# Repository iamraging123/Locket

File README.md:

# Locket
A homemade model rocket with a bunch of cool features

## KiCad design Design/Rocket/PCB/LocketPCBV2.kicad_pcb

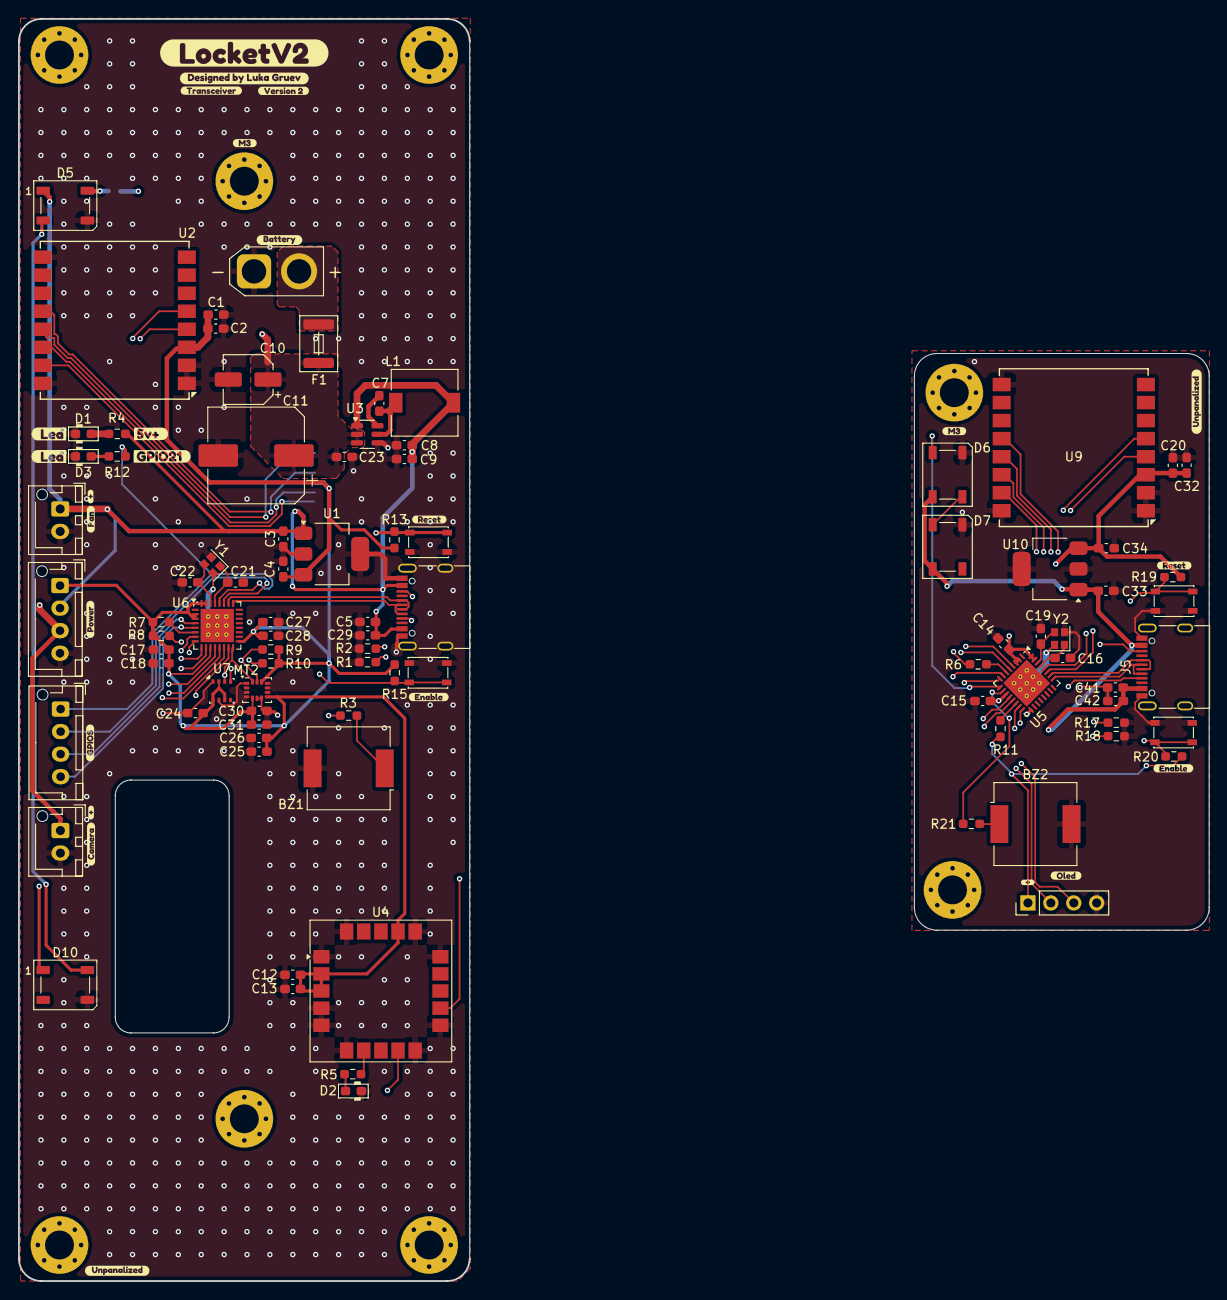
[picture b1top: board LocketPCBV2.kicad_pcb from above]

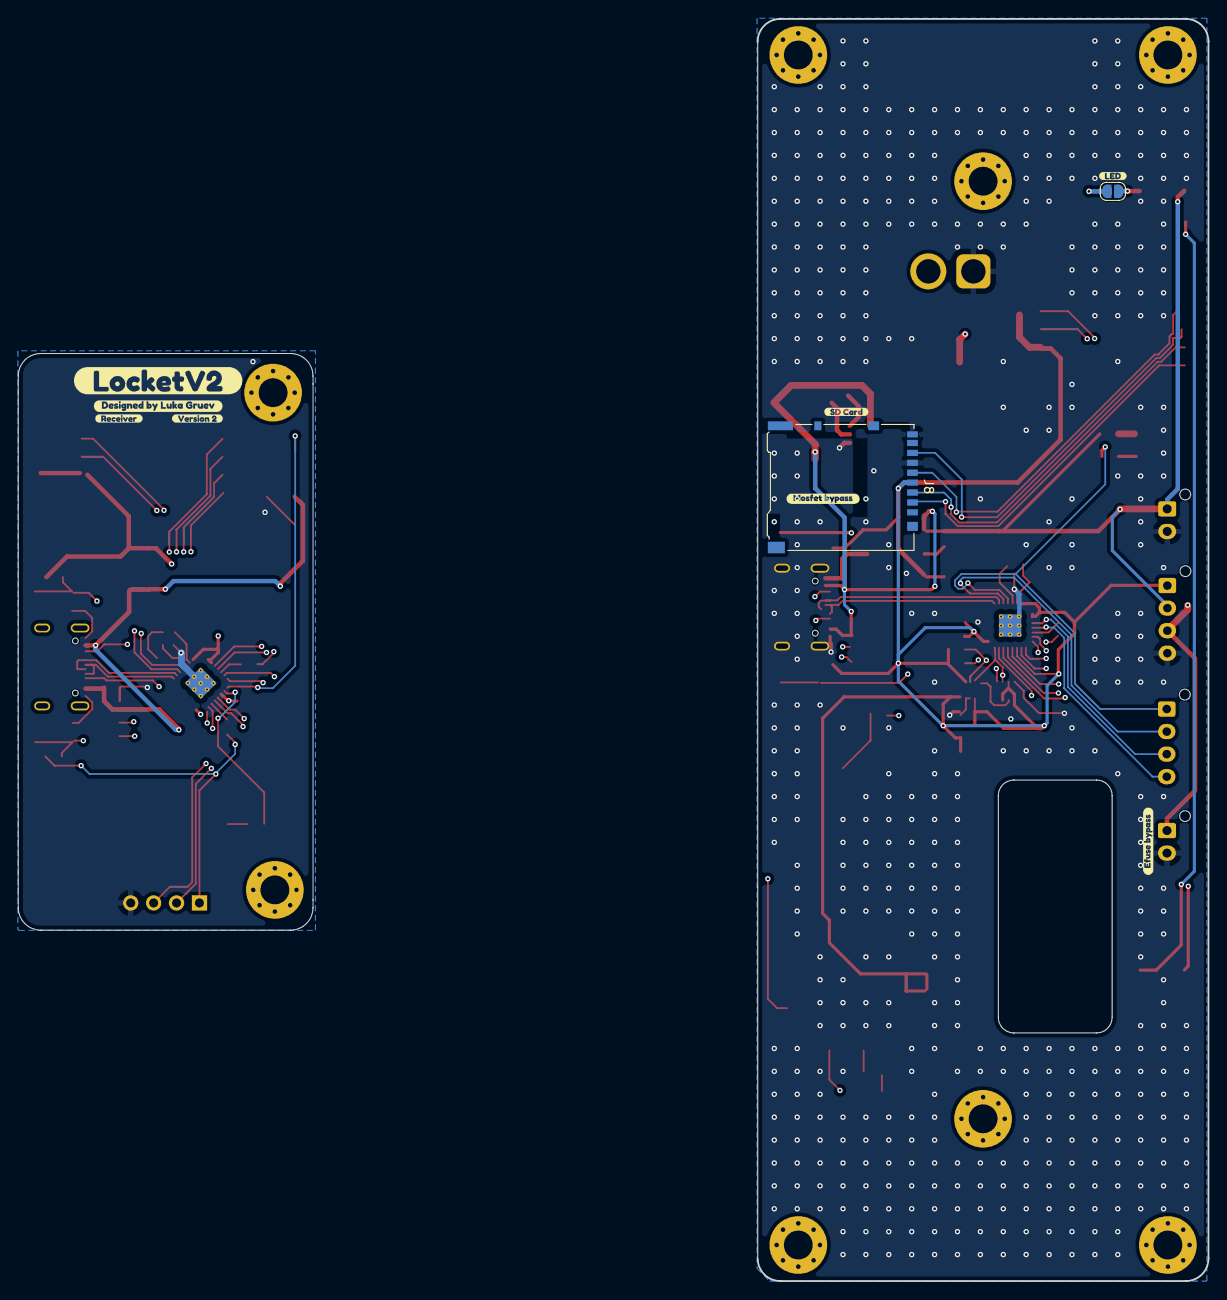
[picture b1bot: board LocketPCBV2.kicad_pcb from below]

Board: 4 copper layers, 132.0 x 140.0 mm, 132 parts (10 on the bottom side), 59 nets.

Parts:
BZ1, BZ2: Buzzer; Buzzer_CUI_CPT-9019S-SMT
C1, C14, C17, C20, C27, C28, C42: 100nf; C_0603_1608Metric_Pad1.08x0.95mm_HandSolder
C2, C15, C32: 10nf; C_0603_1608Metric_Pad1.08x0.95mm_HandSolder
C3, C4, C33, C34: 2uF; C_0603_1608Metric_Pad1.08x0.95mm_HandSolder
C5, C41: 10uf; C_0603_1608Metric_Pad1.08x0.95mm_HandSolder
C7, C12, C18, C30: 100nF; C_0603_1608Metric_Pad1.08x0.95mm_HandSolder
C8, C9: 22uF; C_0603_1608Metric_Pad1.08x0.95mm_HandSolder
C10: 10uF; CP_Elec_5x5.3
C11: 56uF; CP_Elec_10x12.5
C13, C26, C31: 10nF; C_0603_1608Metric_Pad1.08x0.95mm_HandSolder
C16, C19, C21, C22: 14pf; C_0603_1608Metric_Pad1.08x0.95mm_HandSolder
C23: 10uF; C_0603_1608Metric_Pad1.08x0.95mm_HandSolder
C24: 0.1uF; C_0603_1608Metric_Pad1.08x0.95mm_HandSolder
C25: 2.2uF; C_0603_1608Metric_Pad1.08x0.95mm_HandSolder
C29: 1uf; C_0603_1608Metric_Pad1.08x0.95mm_HandSolder
D1, D2, D3: LED; D_0603_1608Metric_Pad1.05x0.95mm_HandSolder
D5, D6, D7, D10: WS2812B; LED_WS2812B_PLCC4_5.0x5.0mm_P3.2mm
F1: Polyfuse_Small; Fuse_1812_4532Metric
H1, H2, H3, H4, H5, H6, H7, H8: MountingHole_M3; MountingHole_3.2mm_M3_Pad_Via
J1, J5: USB_C_Receptacle_USB2.0_14P; USB_C_Receptacle_G-Switch_GT-USB-7010ASV
J2: Conn_01x02_Socket; AMASS_XT30U-F_1x02_P5.0mm_Vertical
J3, J4: Conn_01x04_Socket; JST_XH_B4B-XH-AM_1x04_P2.50mm_Vertical
J6: Conn_01x04_Socket; PinHeader_1x04_P2.54mm_Vertical
J7: Conn_01x02_Socket; JST_XH_B2B-XH-AM_1x02_P2.50mm_Vertical
J8: Micro_SD_Card; microSD_HC_Hirose_DM3AT-SF-PEJM5
JP1: Jumper_2_Open; SolderJumper-2_P1.3mm_Open_RoundedPad1.0x1.5mm
L1: 4.7uH; L_7.3x7.3_H3.5
M1: Fan; JST_XH_B2B-XH-AM_1x02_P2.50mm_Vertical
MT2: ICM-42670-P; LGA-14_3x2.5mm_P0.5mm_LayoutBorder3x4y
R1, R2, R17, R18: 5.1k; R_0603_1608Metric_Pad0.98x0.95mm_HandSolder
R3, R4, R5, R12, R21: 1k; R_0603_1608Metric_Pad0.98x0.95mm_HandSolder
R6, R7, R8, R11, R13, R15, R19, R20: 10k; R_0603_1608Metric_Pad0.98x0.95mm_HandSolder
R9, R10: 2.4k; R_0603_1608Metric_Pad0.98x0.95mm_HandSolder
SW1, SW2, SW3, SW4: SW_MEC_5E; SW_SPST_PTS810
U1, U10: TC1262-33; SOT-223-3_TabPin2
U2, U9: Ai-Thinker-Ra-02; Ai-Thinker-Ra-01-LoRa
U3: AP63205WU; TSOT-23-6
U4: SAM-M8Q; ublox_SAM-M8Q
U5, U6: ESP32-C3; QFN-32-1EP_5x5mm_P0.5mm_EP3.7x3.7mm_ThermalVias
U7: BME280; Bosch_LGA-8_2.5x2.5mm_P0.65mm_ClockwisePinNumbering
Y1, Y2: 40mhz; Crystal_SMD_2016-4Pin_2.0x1.6mm
kibuzzard-689B4DAA: G***; kibuzzard-689B4DAA
kibuzzard-689B4E0F: G***; kibuzzard-689B4E0F
kibuzzard-689B56C6: G***; kibuzzard-689B56C6
kibuzzard-689B56D7: G***; kibuzzard-689B56D7
kibuzzard-689B56E5: G***; kibuzzard-689B56E5
kibuzzard-689B56F2: G***; kibuzzard-689B56F2
kibuzzard-689DD36C: G***; kibuzzard-689DD36C
kibuzzard-689DD368: G***; kibuzzard-689DD368
kibuzzard-689DD373: G***; kibuzzard-689DD373
kibuzzard-689DD379: G***; kibuzzard-689DD379
kibuzzard-689E9224, kibuzzard-689E9224#2: G***; kibuzzard-689E9224
kibuzzard-6840F87B: G***; kibuzzard-6840F87B
kibuzzard-6845CA47: G***; kibuzzard-6845CA47
kibuzzard-6845CAEA: G***; kibuzzard-6845CAEA
kibuzzard-6845D493: G***; kibuzzard-6845D493
kibuzzard-68408A4E, kibuzzard-68408A4E#2: G***; kibuzzard-68408A4E
kibuzzard-68408A06, kibuzzard-68408A06#2: G***; kibuzzard-68408A06
kibuzzard-68408A12, kibuzzard-68408A12#2, kibuzzard-68408A12#3: G***; kibuzzard-68408A12
kibuzzard-68408A39: G***; kibuzzard-68408A39
kibuzzard-684089BD: G***; kibuzzard-684089BD
kibuzzard-684089D7: G***; kibuzzard-684089D7
kibuzzard-684089E4: G***; kibuzzard-684089E4
kibuzzard-684089FE, kibuzzard-684089FE#2: G***; kibuzzard-684089FE
kibuzzard-684241BF, kibuzzard-684241BF#2: G***; kibuzzard-684241BF
kibuzzard-6847062F: G***; kibuzzard-6847062F
kibuzzard-68470665: G***; kibuzzard-68470665

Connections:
+3.3V: C1.2, C2.2, C4.2, C12.1, C13.1, C17.2, C18.2, C24.1, C25.1, C26.1, C27.2, C28.2, C30.1, C31.1, J4.1, J8.4 (VDD), MT2.5 (VDDIO), MT2.8 (VDD), MT2.12 (AP_CS), R7.2, R8.2, R9.2, R10.2, R13.2, R15.2, U1.3 (VO), U2.3 (VDD), U4.2 (VCC_IO), U4.3 (V_BCKP), U4.17 (VCC), U6.2 (VDD3P3), U6.3 (VDD3P3), U6.11 (VDD3P3_RTC), U6.17 (VDD3P3_CPU), U6.31 (VDDA), U6.32 (VDDA), U7.2 (CSB), U7.6 (VDDIO), U7.8 (VDD)
+3.3VR: C14.2, C15.2, C20.2, C32.2, C34.2, J6.1, R6.2, R11.2, R19.2, R20.2, U5.2 (VDD3P3), U5.3 (VDD3P3), U5.11 (VDD3P3_RTC), U5.17 (VDD3P3_CPU), U5.31 (VDDA), U5.32 (VDDA), U9.3 (VDD), U10.3 (VO)
+5V: C3.2, C5.2, C8.2, C9.2, C29.2, D5.1 (VDD), D10.1 (VDD), J1.A4 (VBUS), J1.A9 (VBUS), J1.B4 (VBUS), J1.B9 (VBUS), J4.2, L1.2, M1.1 (+), R4.2, U1.1 (VI), U3.1 (FB)
+5VR: C33.2, C41.2, C42.2, D6.1 (VDD), D7.1 (VDD), J5.A4 (VBUS), J5.A9 (VBUS), J5.B4 (VBUS), J5.B9 (VBUS), U10.1 (VI)
+BATT: C10.1, C11.1, C23.2, F1.1, J4.3, J7.1, U3.2 (EN), U3.3 (IN)
D+: J1.A6 (D+), J1.B6 (D+), U6.26 (GPIO19)
D+R: J5.A6 (D+), J5.B6 (D+), U5.26 (GPIO19)
D-: J1.A7 (D-), J1.B7 (D-), U6.25 (GPIO18)
D-R: J5.A7 (D-), J5.B7 (D-), U5.25 (GPIO18)
DIN: MT2.14 (AP_SDA/AP_SDIO/AP_SDI), R10.1, U4.9 (SDA), U6.16 (GPIO10), U7.3 (SDI)
DINR: J6.3, U5.16 (GPIO10)
DOUT: MT2.13 (AP_SCL/AP_SCLK), R9.1, U4.12 (SCL), U6.8 (GPIO3), U7.4 (SCK)
DOUTR: J6.2, U5.8 (GPIO3)
Enable: R15.1, SW4.1, U6.7 (CHIP_EN)
EnableR: R20.1, SW2.1, U5.7 (CHIP_EN)
GND1: BZ1.2 (-), C1.1, C2.1, C3.1, C4.1, C5.1, C8.1, C9.1, C10.2, C11.2, C12.2, C13.2, C17.1, C18.1, C21.1, C22.1, C23.1, C24.2, C25.2, C26.2, C27.1, C28.1, C29.1, C30.2, C31.2, D1.1, D2.1, D3.1, D5.3 (VSS), D10.3 (VSS), J1.A1 (GND), J1.A12 (GND), J1.B1 (GND), J1.B12 (GND), J2.1, J4.4, J7.2, J8.6 (VSS), J8.9 (SHIELD), M1.2 (-), MT2.1 (AP_SDO/AP_AD0), MT2.6 (GND), MT2.7 (FSYNC), R1.2, R2.2, SW3.2, SW4.2, U1.2 (GND), U2.1 (GND), U2.2 (GND), U2.9 (GND), U2.16 (GND), U3.4 (GND), U4.1 (GND), U4.4 (GND), U4.5 (GND), U4.6 (GND), U4.10 (GND), U4.11 (GND), U4.15 (GND), U4.16 (GND), U4.20 (GND), U6.33 (GND), U7.1 (GND), U7.7 (GND), Y1.2, Y1.4
GND2: BZ2.2 (-), C14.1, C15.1, C16.1, C19.1, C20.1, C32.1, C33.1, C34.1, C41.1, C42.1, D6.3 (VSS), D7.3 (VSS), J5.A1 (GND), J5.A12 (GND), J5.B1 (GND), J5.B12 (GND), J6.4, R17.2, R18.2, SW1.2, SW2.2, U5.33 (GND), U9.1 (GND), U9.2 (GND), U9.9 (GND), U9.16 (GND), U10.2 (GND), Y2.2, Y2.4
GPIO0: J3.3, J8.2 (DAT3/CD), U2.15 (~NSS), U6.4 (XTAL_32K_P)
GPIO0R: U5.4 (XTAL_32K_P), U9.4 (~RESET)
GPIO1: J3.4, U2.5 (DIO0), U6.5 (XTAL_32K_N)
GPIO1R: U5.5 (XTAL_32K_N), U9.5 (DIO0)
GPIO2: R7.1, U6.6 (GPIO2)
GPIO4: U2.4 (~RESET), U6.9 (MTMS)
GPIO4R: D6.4 (DIN), U5.9 (MTMS)
GPIO5: J8.3 (CMD), U2.14 (MOSI), U6.10 (MTDI)
GPIO5R: R21.1, U5.10 (MTDI)
GPIO6: J8.7 (DAT0), U2.13 (MISO), U6.12 (MTCK)
GPIO7: J8.5 (CLK), U2.12 (SCK), U6.13 (MTDO)
GPIO8: R3.1, R8.1, U6.14 (GPIO8)
GPIO20: J3.2, U6.27 (U0RXD)
GPIO21: J3.1, R12.2, U6.28 (U0TXD)
MISOR: U5.28 (U0TXD), U9.14 (MOSI)
MOSIR: U5.27 (U0RXD), U9.13 (MISO)
unnamed: BZ1.1 (+), R3.2
unnamed: BZ2.1 (+), R21.2
unnamed: D1.2, R4.1
unnamed: D2.2, R5.1
unnamed: D3.2, R12.1
unnamed: D5.4 (DIN), JP1.2 (B)
unnamed: D6.2 (DOUT), D7.4 (DIN)
unnamed: D5.2 (DOUT), D10.4 (DIN)
unnamed: J1.A5 (CC1), R2.1
unnamed: J1.B5 (CC2), R1.1
unnamed: F1.2, J2.2
unnamed: J5.A5 (CC1), R18.1
unnamed: J5.B5 (CC2), R17.1
unnamed: C7.1, U3.6 (BST)
unnamed: C7.2, L1.1, U3.5 (SW)
unnamed: R5.2, U4.7 (TIMEPULSE)
unnamed: R6.1, U5.6 (GPIO2)
unnamed: R11.1, U5.14 (GPIO8)
unnamed: C16.2, U5.29 (XTAL_N), Y2.1
unnamed: C19.2, U5.30 (XTAL_P), Y2.3
unnamed: C21.2, U6.29 (XTAL_N), Y1.1
unnamed: C22.2, U6.30 (XTAL_P), Y1.3
Reset: JP1.1 (A), R13.1, SW3.1, U6.15 (GPIO9)
ResetR: R19.1, SW1.1, U5.15 (GPIO9)
SPICLKR: U5.13 (MTDO), U9.12 (SCK)
SPICSR: U5.12 (MTCK), U9.15 (~NSS)

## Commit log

2025-09-14 Create GraphAllMain
2025-10-05 Update and rename GraphAllMain to code/PythonReceiverDashboard
2025-10-05 Rename code/PythonReceiverDashboard to Code/Transmitter/PythonReceiverDashboard
2025-10-05 Create ReceiverMain
2025-10-05 Rename Code/Transmitter/PythonReceiverDashboard to Code/Receiver/Python/ReceiverApplicationCode
2025-10-05 Create TransmitterCode
2025-10-13 Update ReceiverApplicationCode
2025-10-13 Update TransmitterCode
2025-10-13 Update ReceiverMain
2025-10-13 Create OpenRocket
2025-10-13 Rename LocketV1.3.0.ork to Design/OpenRocket/LocketV1.3.0.ork
2025-10-13 Rename LocketCadV1.step to Design/Cad/LocketCadV1.step
2025-10-13 Rename Design/OpenRocket/LocketV1.3.0.ork to Design/Rocket/OpenRocket/LocketV1.3.0.ork
2025-10-13 Rename LocketTransmitterAssemblyV1.step to Design/Transmitter/LocketTransmitterAssemblyV1.step
2025-10-13 Rename LocketPCBv2.kicad_pro to Design/Rocket/PCB/LocketPCBv2.kicad_pro
2025-10-13 Rename Top.png to Photos/Renders/Top.png
2025-10-13 Rename Turntable.mp4 to Photos/Renders/Turntable.mp4
2025-10-13 Rename cool.png to Photos/Renders/TopRight.png
2025-10-13 Rename second.png to Photos/Renders/Front.png
